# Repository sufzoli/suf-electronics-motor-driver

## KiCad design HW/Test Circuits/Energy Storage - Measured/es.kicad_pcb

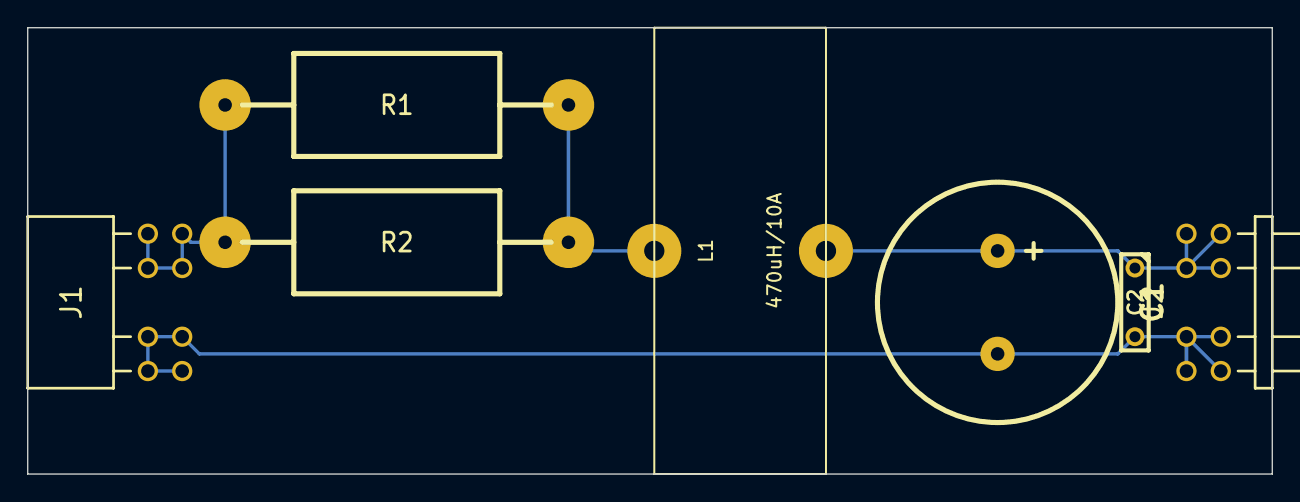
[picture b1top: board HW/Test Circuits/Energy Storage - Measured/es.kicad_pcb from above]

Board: 2 copper layers, 92.1 x 33.0 mm, 7 parts (0 on the bottom side), 4 nets.

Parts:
C1: 1000uF/63V; C3P_D7
C2: 10nF/100V; C2
J1: IN; MD-TEST-HDR-F
J2: OUT; MD-TEST-HDR-M
L1: 470uH/10A; L-TOROID-D35X5
R1, R2: 0R1/5W; R10

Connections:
GND: C1.2, C2.2, J1.1, J1.2, J1.3, J1.4, J2.1, J2.2, J2.3, J2.4
unnamed: L1.1, R1.2, R2.2
unnamed: C1.1, C2.1, J2.7, J2.8, J2.9, J2.10, L1.2
unnamed: J1.7, J1.8, J1.9, J1.10, R1.1, R2.1

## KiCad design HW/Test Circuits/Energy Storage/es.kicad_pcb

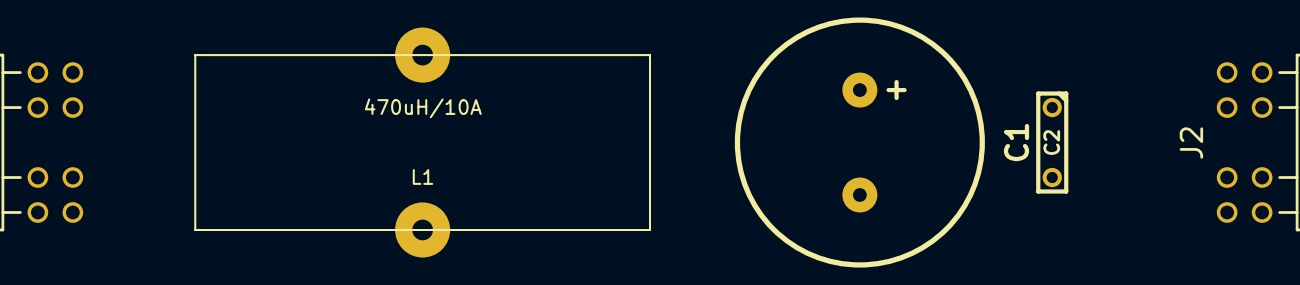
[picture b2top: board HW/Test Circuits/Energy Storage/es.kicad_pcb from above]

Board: 2 copper layers, 5 parts (0 on the bottom side), 3 nets, no tracks yet.

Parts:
C1: 1000uF/63V; C3P_D7
C2: 10nF/100V; C2
J1: IN; MD-TEST-HDR-F
J2: OUT; MD-TEST-HDR-M
L1: 470uH/10A; L-TOROID-D35X5

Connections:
GND: C1.2, C2.2, J1.7, J1.8, J1.9, J1.10, J2.7, J2.8, J2.9, J2.10
unnamed: J1.1, J1.2, J1.3, J1.4, L1.1
unnamed: C1.1, C2.1, J2.1, J2.2, J2.3, J2.4, L1.2

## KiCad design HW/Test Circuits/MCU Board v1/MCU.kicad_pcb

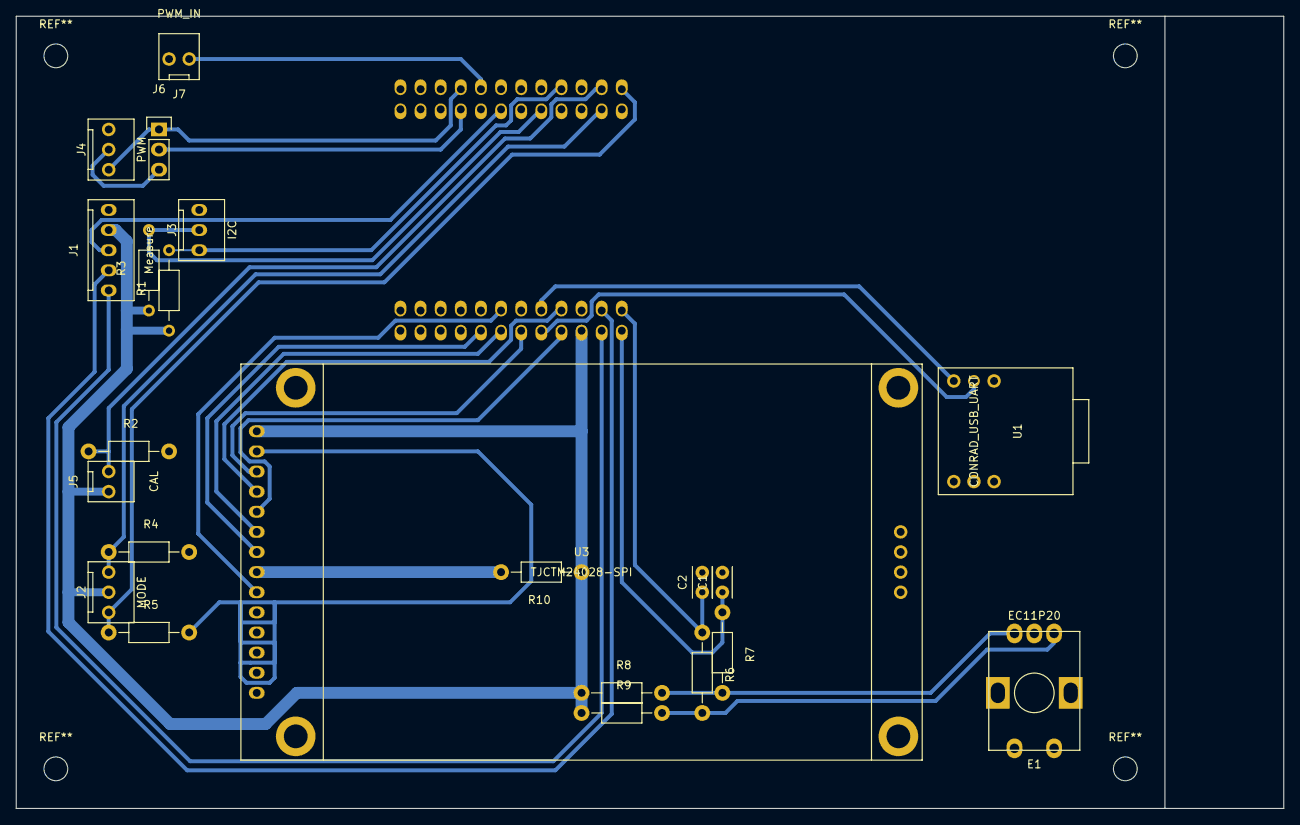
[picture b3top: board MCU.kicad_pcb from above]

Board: 2 copper layers, 160.0 x 100.0 mm, 23 parts (1 on the bottom side), 27 nets.

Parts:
C1, C2: 10nF; C_Rect_L4_W2.5_P2.5
E1: EC11P20; EC11P20_single_side
J1: Measure; CONN_NCW254-05S
J2: MODE; CONN_NCW254-03S
J3: I2C; CONN_NCW254-03S
J4: PWM; CONN_NCW254-03S
J5: CAL; CONN_NCW254-02S
J6: PWM_DUAL; Pin_Header_Straight_1x03
J7: PWM_IN; CONN_NCW254-02S
R1, R3, R6, R7, R8, R9: 10K; Resistor_Horizontal_RM10mm
R2, R4, R5: 47K; Resistor_Horizontal_RM10mm
R10: 3R9; Resistor_Horizontal_RM10mm
U1: CONRAD_USB_UART
U2: M0516LDN; M0516-DEV
U3: TJCTM24028-SPI

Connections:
ADC_I: J1.2, U2.40
ADC_U: J1.1, U2.39
CAL: J5.2, R2.1, U2.33
ENC_A: C2.1, R6.1, U2.38
ENC_B: C1.1, R7.1, U2.37
GND: C1.2, C2.2, E1.1, J1.5, J3.3, J4.3, J7.2, R2.2, R4.2, R5.2, U1.1, U1.5, U2.17, U3.2
I2C_SCL: J3.2, R3.2, U2.28
I2C_SDA: J3.1, R1.2, U2.29
MODE_AUTO: J2.3, R4.1, U2.34
MODE_RPM: J2.1, R5.1, U2.35
unnamed: E1.2, R6.2, R9.2
unnamed: E1.3, R7.2, R8.2
unnamed: J4.2, J6.3
unnamed: R10.2, U3.8
PWM_0: J4.1, J6.1, U2.19
PWM_1: J6.2, U2.20
RPM_CTRL: J7.1, U2.21
RPM_IN: J1.3, U2.24
RXD: U1.2, U2.45
TFT_CS: U2.47, U3.3
TFT_DC: U2.43, U3.5
TFT_MISO: U2.2, U3.9
TFT_MOSI: U2.1, U3.6
TFT_RST: U2.44, U3.4
TFT_SCK: U2.3, U3.7
TXD: U1.3, U2.46
VCC: J1.4, J2.2, J5.1, R1.1, R3.1, R8.1, R9.1, R10.1, U2.41, U3.1

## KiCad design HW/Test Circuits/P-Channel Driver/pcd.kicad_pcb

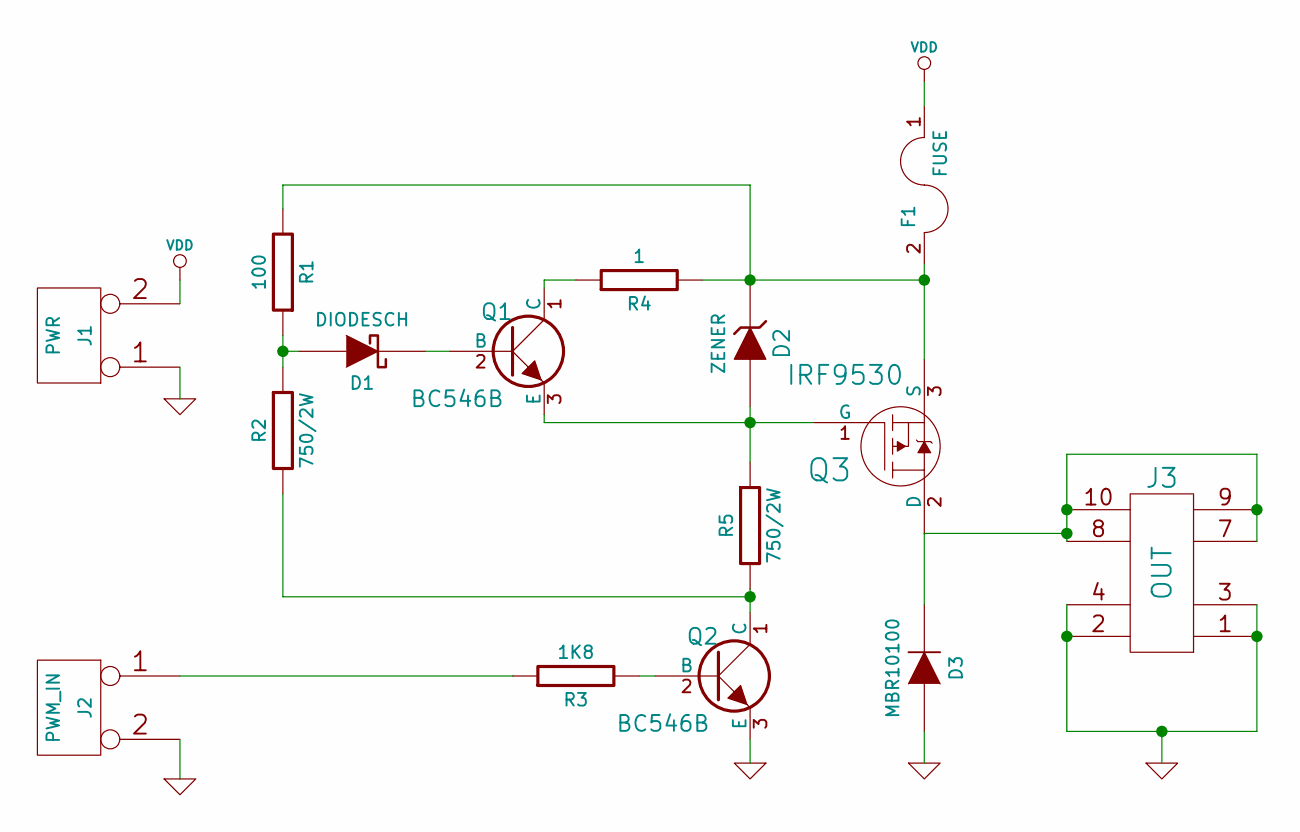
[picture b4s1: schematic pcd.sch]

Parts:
D1: DIODESCH; D2
D2: ZENER; D2
D3: MBR10100; TO220-2
F1: FUSE; AUTOFUSE
J1: PWR; MOLEX_36538_2
J2: PWM_IN; CONN_NCW254-02S
J3: OUT; MD-TEST-HDR-M
Q1, Q2: BC546B; TO-92_V
Q3: IRF9530; TO-220_V
R1: 100; R4
R2, R5: 750/2W; R6
R3: 1K8; R4
R4: 1; R4

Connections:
GND: D3.3 (A), J1.1, J2.2 (PM), J3.1, J3.2, J3.3, J3.4, Q2.3 (E)
unnamed: J2.1, R3.2
unnamed: Q2.1 (C), R2.1, R5.1
unnamed: D2.2 (K), F1.2, Q3.3 (S), R1.1, R4.1
unnamed: D3.1 (K), J3.7, J3.8, J3.9, J3.10, Q3.2 (D)
unnamed: Q2.2 (B), R3.1
unnamed: D2.1 (A), Q1.3 (E), Q3.1 (G), R5.2
unnamed: D1.1 (A), R1.2, R2.2
unnamed: D1.2 (K), Q1.2 (B)
unnamed: Q1.1 (C), R4.2
VDD: F1.1, J1.2 (PM)

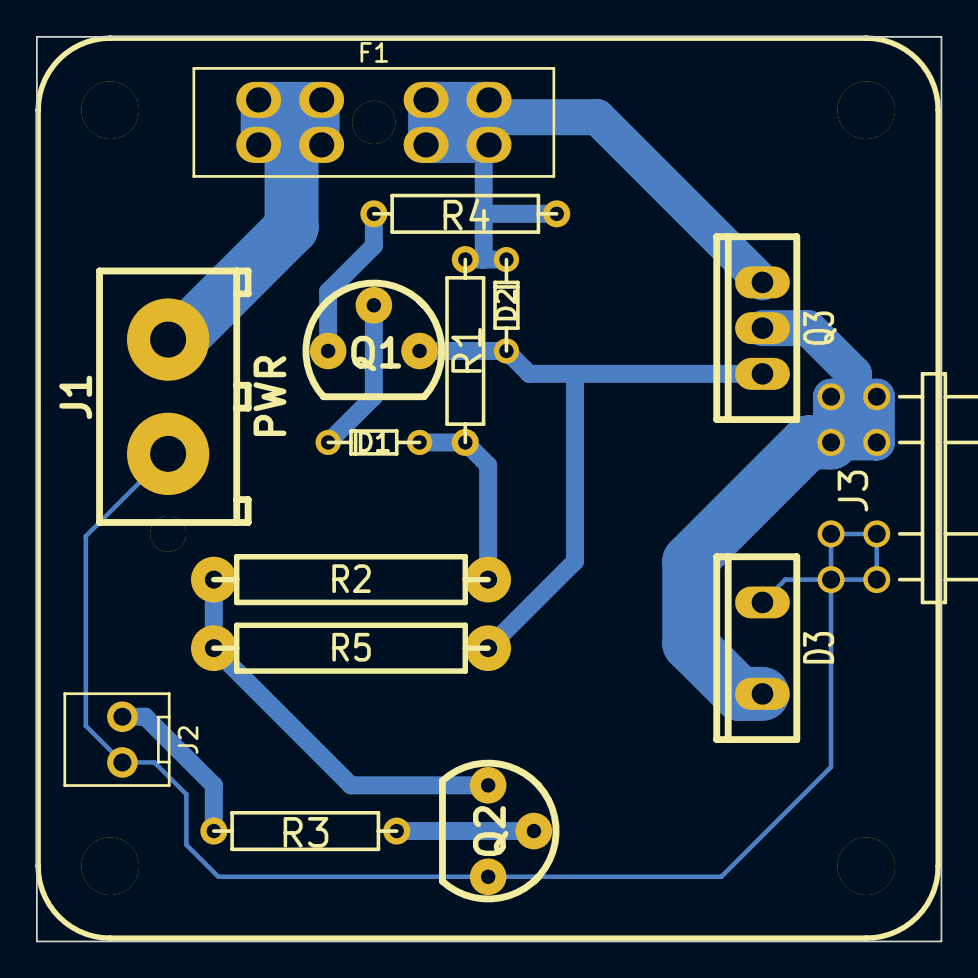
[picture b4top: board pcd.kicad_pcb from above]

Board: 2 copper layers, 50.3 x 50.2 mm, 16 parts (0 on the bottom side), 11 nets.

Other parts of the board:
DP5050: DP5050
